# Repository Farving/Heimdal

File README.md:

# IAQ-monitor
Indoor Air Quality monitor

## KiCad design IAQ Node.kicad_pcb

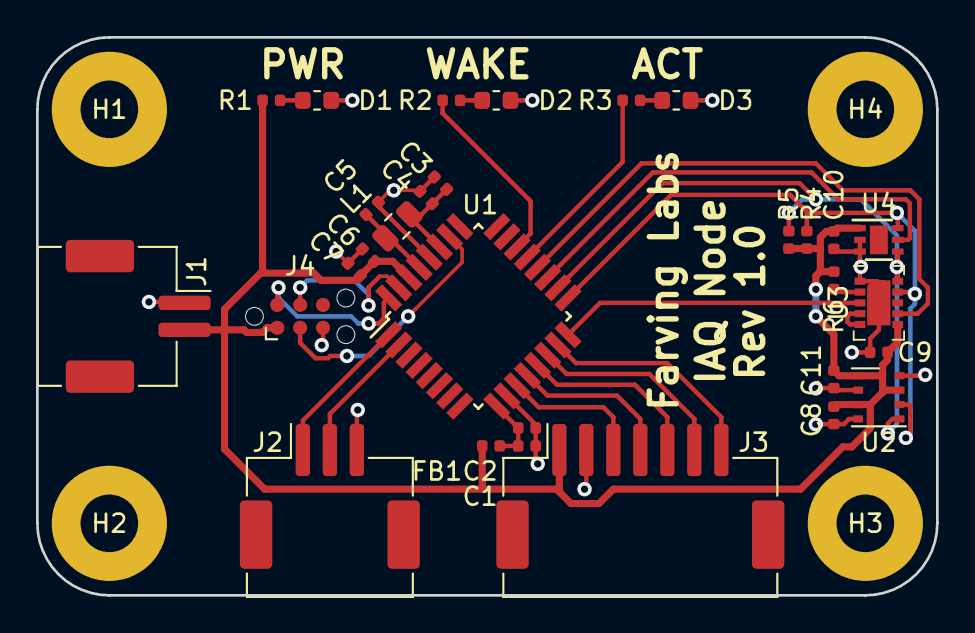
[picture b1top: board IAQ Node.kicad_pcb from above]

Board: 2 copper layers, 50.0 x 31.0 mm, 34 parts (0 on the bottom side), 27 nets.

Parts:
C1, C7: 4u7; C_0402_1005Metric
C2, C4, C6, C8, C10, C11: 100n; C_0402_1005Metric
C3, C5, C9: 1u; C_0402_1005Metric
D1, D2, D3: LED_Small; R_0603_1608Metric
FB1: Ferrite_Bead_Small; L_0402_1005Metric
H1, H2, H3, H4: MountingHole_Pad; MountingHole_3.2mm_M3_Pad
J1: JST S2B-ZR-SMA4-TF; JST_ZE_SM02B-ZESS-TBT_1x02-1MP_P1.50mm_Horizontal
J2: JST S3B-ZR-SMA4-TF; JST_ZE_SM03B-ZESS-TBT_1x03-1MP_P1.50mm_Horizontal
J3: JST S7B-ZR-SMA4-TF; JST_ZE_SM07B-ZESS-TBT_1x07-1MP_P1.50mm_Horizontal
J4: TC2030-CTX-NL; Tag-Connect_TC2030-IDC-NL_2x03_P1.27mm_Vertical
L1: 10uH; L_0805_2012Metric
R1, R2, R3: R_Small; R_0402_1005Metric
R4, R5: 2k2; R_0402_1005Metric
R6: 4k7; R_0402_1005Metric
U1: ATSAML21E18B-AUT; TQFP-32_7x7mm_P0.8mm
U2: BME680; Bosch_LGA-8_3x3mm_P0.8mm_ClockwisePinNumbering
U3: CCS811; AMS_LGA-10-1EP_2.7x4mm_P0.6mm
U4: OPT3001; DFN-6-1EP_2x2mm_P0.65mm_EP1x1.6mm

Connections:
/BUSY: J3.7, U1.15
/CCS81_WAKE: U1.20, U3.7
/CLK: J3.3, U1.11
/CS: J3.4, U1.12
/CSS811_INT: U1.16, U3.3
/D_C: J3.6, U1.14
/I2C_SCL: R5.2, U1.18, U2.4, U3.10, U4.4
/I2C_SDA: R4.2, U1.17, U2.3, U3.9, U4.6
/LED1: R2.1, U1.22
/LED2: R3.1, U1.21
/OPT3001_INT: U1.19, U4.5
/RESET: J4.3, U1.26
/SDI: J3.5, U1.13
/SWCLK: J4.4, U1.31
/SWDIO: J4.2, U1.32
/UART_RX: J2.1, U1.1
/UART_TX: J2.2, U1.2
/VDDA: C1.1, C2.1, FB1.1, U1.9
/VDDCORE: C3.1, C4.1, L1.1, U1.27
/VSW: C5.1, L1.2, U1.29
GND: C1.2, C2.2, C3.2, C4.2, C5.2, C6.2, C7.2, C8.2, C9.2, C10.2, C11.2, D1.1, D2.1, D3.1, J1.1, J2.3, J3.2, J4.5, U1.10, U1.28, U2.1, U2.5, U2.7, U3.1, U3.11, U4.2, U4.3
unnamed: D1.2, R1.2
unnamed: D2.2, R2.2
unnamed: D3.2, R3.2
unnamed: R6.2, U3.2
unnamed: U3.4, U3.5
VDD: C6.1, C7.1, C8.1, C9.1, C10.1, C11.1, FB1.2, J1.2, J3.1, J4.1, R1.1, R4.1, R5.1, R6.1, U1.30, U2.2, U2.6, U2.8, U3.6, U4.1

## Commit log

2018-10-29 Update LICENSE
2018-10-30 Added Project
    Add MCU
    Add CCS811
    Add BME680
    Add Connectors
    Add outline (incorrect)
    Updated PCB from schematic
2018-11-09 Alpha release of PCB
2018-11-25 Changed connector
    Removed JST 8way
    Added Tag-connect SWD connector
    Added JST 3way for UART
    Major layout changes
